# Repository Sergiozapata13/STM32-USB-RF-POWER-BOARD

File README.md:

# STM32-USB-RF-POWER-BOARD

## Overview
STM32-based embedded board integrating USB, RF transceiver, and regulated power supply.
Designed in KiCad with focus on signal integrity, power distribution, EMI mitigation, and
robust hardware design practices.

The project demonstrates a complete PCB design workflow, from system architecture
definition and schematic design to PCB layout and manufacturability review.

---

## System Architecture
The board integrates the following functional blocks:

- STM32 microcontroller
- USB interface for power and data communication
- nRF24L01+ 2.4 GHz RF transceiver
- Regulated 3.3 V power supply derived from USB
- SWD interface for programming and debugging

---

## Power Architecture

The board is powered exclusively from the USB 5 V rail. Input protection is provided
by a resettable fuse (100 mA) and a ferrite bead (100 Ω @ 100 MHz) to limit overcurrent
conditions and attenuate high-frequency noise coming from the USB source.

A low-dropout linear regulator (XC6206P332MR) is used to generate the 3.3 V supply
required by the STM32 microcontroller and the RF transceiver. This regulator was
selected due to its low noise characteristics and simplicity, which are well suited
for low-current embedded applications (up to 200 mA).

Bulk capacitors are placed at both the regulator input and output to ensure stability
and reduce supply ripple. Reverse polarity protection was intentionally omitted, as the
USB connector is the only intended power source for the board.

---

## USB Design

The USB interface is implemented using a Micro-USB connector and provides both power
and data connectivity. The VBUS line is used as the sole power source for the board.

Electrostatic discharge (ESD) protection is provided by a USBLC6-2SC6 device placed
between the USB connector and the microcontroller. This device protects the D+ and D−
lines against ESD events while preserving signal integrity.

USB differential data lines are routed as a matched pair and clearly labeled to support
controlled impedance routing during PCB layout. Protection components are placed close
to the connector to minimize trace length and reduce exposure to ESD events.

---

## RF Design

The RF subsystem is based on the nRF24L01+ 2.4 GHz transceiver, interfaced with the STM32
microcontroller through an SPI interface. The device is powered from the 3.3 V rail,
with dedicated local decoupling capacitors placed close to the VDD and VDD_PA pins to
ensure stable RF operation.

Special attention was given to power integrity for the RF section by providing adequate
bulk and high-frequency decoupling and following manufacturer reference design
guidelines.

### Antenna Matching Network

The RF output is routed through a discrete impedance matching network before reaching
an SMA connector. The matching network is implemented using lumped inductors and
capacitors, allowing flexibility for tuning during bring-up or testing.

The RF trace is intended to be routed as a 50 Ω controlled-impedance transmission line.
Component placement and routing were optimized to keep the RF path as short and direct
as possible, minimizing losses and parasitic effects.

### RF Crystal Oscillator

A dedicated 16 MHz crystal oscillator is used for the RF transceiver. Load capacitors
were selected based on the required load capacitance and estimated stray capacitance
of the PCB layout. A parallel resistor is included to aid oscillator startup and
improve stability.

Crystal components are placed close to the transceiver pins with short, symmetric
traces to minimize phase noise and sensitivity to external interference.

---

## PCB Layout Strategy

The PCB layout was developed with emphasis on signal integrity, power distribution,
and noise isolation between digital, RF, and power domains. Component placement was
driven by functional grouping, minimizing critical trace lengths and optimizing return
current paths.

High-frequency and noise-sensitive components, such as the RF transceiver and its
matching network, are placed close together to reduce parasitic effects. Power-related
components are grouped to form compact current loops, reducing EMI and voltage ripple.

USB differential pairs are routed together with consistent spacing and length matching,
and ground continuity is maintained under high-speed signals to ensure a clear return
path.

A compact board outline was selected to balance mechanical constraints, routing density,
and manufacturability.

---

## Hardware Validation and Design Status

The PCB was fully designed and reviewed at schematic and layout level; however, the
board was not manufactured or assembled.

Design validation focused on schematic correctness, component selection, and layout
best practices. Electrical rules checks (ERC) and design rule checks (DRC) were used to
verify connectivity, clearance, and manufacturability constraints.

The design is considered ready for fabrication. A bring-up and validation plan was
defined, including power rail verification, SWD programming, USB enumeration, and basic
RF communication tests.

Although physical validation was not performed, the project demonstrates a complete
end-to-end PCB design workflow, from system architecture definition to layout completion.

---

## Tools
- KiCad
- STM32CubeMX (pinout and reference configuration)

---

## Project Status
- Schematic and PCB layout completed
- Design reviewed with ERC/DRC verification
- Ready for fabrication

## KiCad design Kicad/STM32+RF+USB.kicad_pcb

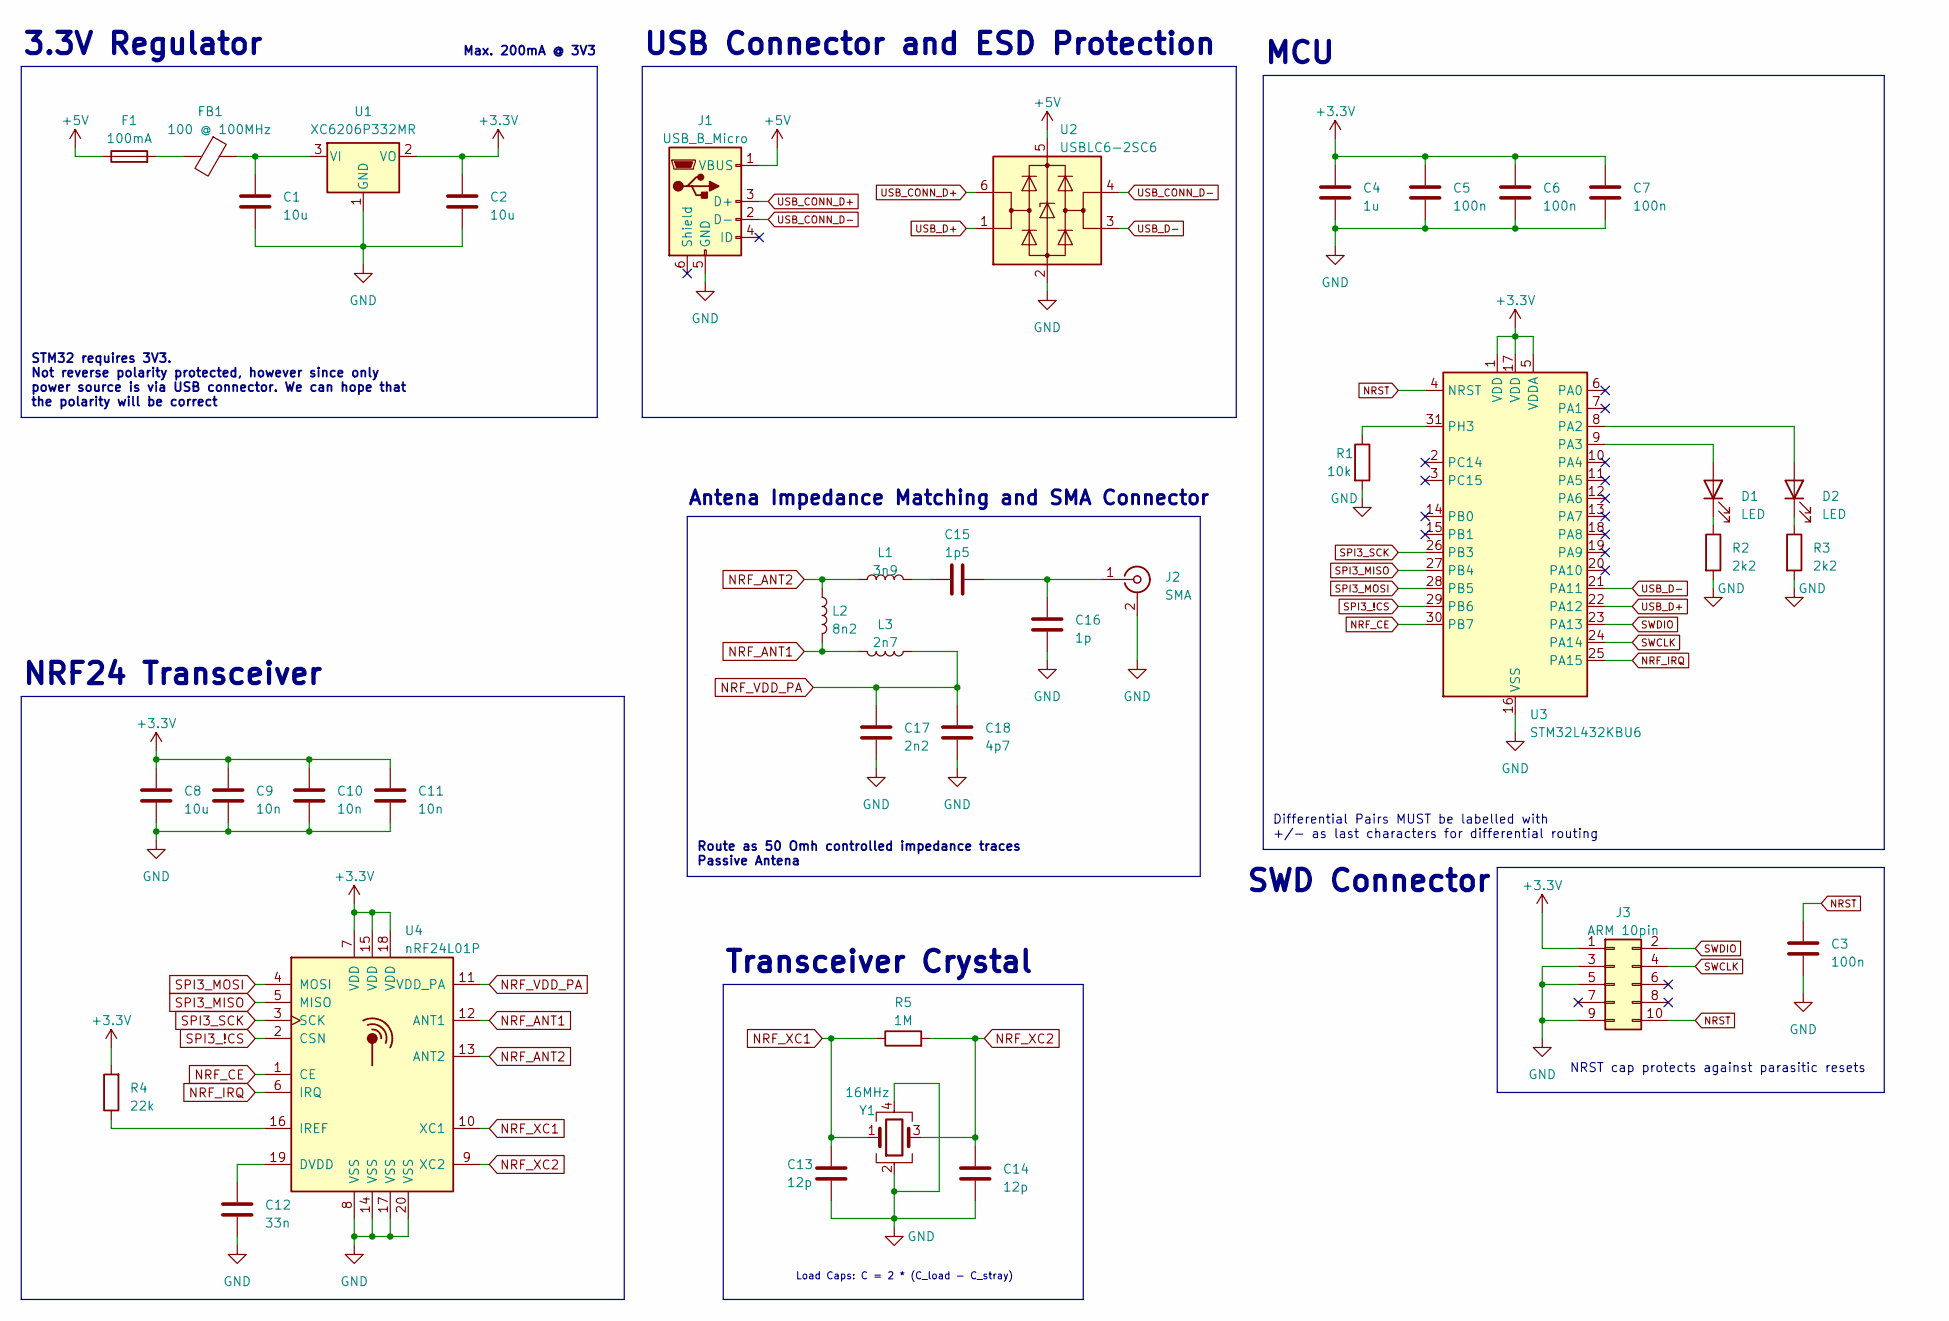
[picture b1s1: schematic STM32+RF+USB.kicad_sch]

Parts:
C1, C2, C8: 10u; C_0603_1608Metric
C3, C5, C6, C7: 100n; C_0402_1005Metric
C4: 1u; C_0402_1005Metric
C9, C10, C11: 10n; C_0402_1005Metric
C12: 33n; C_0402_1005Metric
C13, C14: 12p; C_0402_1005Metric
C15: 1p5; C_0402_1005Metric
C16: 1p; C_0402_1005Metric
C17: 2n2; C_0402_1005Metric
C18: 4p7; C_0402_1005Metric
D1, D2: LED; LED_0603_1608Metric
F1: 100mA; Fuse_1206_3216Metric
FB1: 100 @ 100MHz; L_0805_2012Metric
J1: USB_B_Micro; USB_Micro-B_Molex-105017-0001
J2: SMA; SMA_Samtec_SMA-J-P-X-ST-EM1_EdgeMount
J3: ARM 10pin; PinHeader_2x05_P1.27mm_Vertical
L1: 3n9; L_0402_1005Metric
L2: 8n2; L_0402_1005Metric
L3: 2n7; L_0402_1005Metric
R1: 10k; R_0402_1005Metric
R2, R3: 2k2; R_0603_1608Metric
R4: 22k; R_0402_1005Metric
R5: 1M; R_0402_1005Metric
U1: XC6206P332MR; SOT-23-3
U2: USBLC6-2SC6; SOT-23-6
U3: STM32L432KBU6; QFN-32-1EP_5x5mm_P0.5mm_EP3.45x3.45mm
U4: nRF24L01P; QFN-20-1EP_4x4mm_P0.5mm_EP2.5x2.5mm
Y1: 16MHz; Crystal_SMD_3225-4Pin_3.2x2.5mm

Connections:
+3.3V: C2.1, C4.1, C5.1, C6.1, C7.1, C8.1, C9.1, C10.1, C11.1, J3.1, R4.2, U1.2 (VO), U3.1 (VDD), U3.5 (VDDA), U3.17 (VDD), U4.7 (VDD), U4.15 (VDD), U4.18 (VDD)
+5V: F1.1, J1.1 (VBUS), U2.5 (VBUS)
GND: C1.2, C2.2, C3.2, C4.2, C5.2, C6.2, C7.2, C8.2, C9.2, C10.2, C11.2, C12.2, C13.2, C14.2, C16.1, C17.1, C18.1, J1.5 (GND), J2.2 (Ext), J3.3, J3.5, J3.9, R1.2, R2.2, R3.2, U1.1 (GND), U2.2 (GND), U3.16 (VSS), U3.32 (VSS), U3.33 (VSS), U4.8 (VSS), U4.14 (VSS), U4.17 (VSS), U4.20 (VSS), Y1.2, Y1.4
NRF_ANT1: L2.2, L3.2, U4.12 (ANT1)
NRF_ANT2: L1.1, L2.1, U4.13 (ANT2)
NRF_CE: U3.30 (PB7), U4.1 (CE)
NRF_IRQ: U3.25 (PA15), U4.6 (IRQ)
NRF_VDD_PA: C17.2, C18.2, L3.1, U4.11 (VDD_PA)
NRF_XC1: C13.1, R5.1, U4.10 (XC1), Y1.1
NRF_XC2: C14.1, R5.2, U4.9 (XC2), Y1.3
NRST: C3.1, J3.10, U3.4 (NRST)
unnamed: C15.1, L1.2
unnamed: D1.2 (A), U3.9 (PA3)
unnamed: D1.1 (K), R2.1
unnamed: D2.2 (A), U3.8 (PA2)
unnamed: D2.1 (K), R3.1
unnamed: F1.2, FB1.2
unnamed: C15.2, C16.2, J2.1 (In)
unnamed: C1.1, FB1.1, U1.3 (VI)
unnamed: R1.1, U3.31 (PH3)
unnamed: C12.1, U4.19 (DVDD)
unnamed: R4.1, U4.16 (IREF)
SPI3_!CS: U3.29 (PB6), U4.2 (CSN)
SPI3_MISO: U3.27 (PB4), U4.5 (MISO)
SPI3_MOSI: U3.28 (PB5), U4.4 (MOSI)
SPI3_SCK: U3.26 (PB3), U4.3 (SCK)
SWCLK: J3.4, U3.24 (PA14)
SWDIO: J3.2, U3.23 (PA13)
USB_CONN_D+: J1.3 (D+), U2.6 (I/O1)
USB_CONN_D-: J1.2 (D-), U2.4 (I/O2)
USB_D+: U2.1 (I/O1), U3.22 (PA12)
USB_D-: U2.3 (I/O2), U3.21 (PA11)

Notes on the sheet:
Load Caps: C = 2 * (C_load - C_stray)
Max. 200mA @ 3V3
SWD Connector
Differential Pairs MUST be labelled with +/- as last characters for differential routing
Transceiver Crystal
USB Connector and ESD Protection
STM32 requires 3V3. Not reverse polarity protected, however since only power source is via USB connector. We can hope that the polarity will be correct
Route as 50 Omh controlled impedance traces Passive Antena
MCU
Antena Impedance Matching and SMA Connector
NRST cap protects against parasitic resets
NRF24 Transceiver
3.3V Regulator

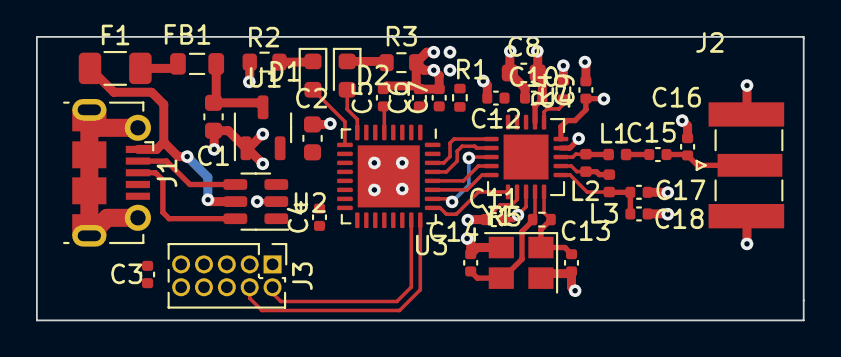
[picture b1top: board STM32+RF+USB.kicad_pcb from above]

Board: 4 copper layers, 42.6 x 15.8 mm, 38 parts (0 on the bottom side), 32 nets.

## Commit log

2026-01-22 Enhance README with detailed project information
    Expanded the README with sections on system architecture, power architecture, USB design, RF design, PCB layout strategy, hardware validation, tools, and project status.
2026-01-23 Document power architecture in README
    Added detailed explanation of the power architecture, including design considerations for voltage regulation and noise performance.
2026-01-23 Refine power architecture description in README
    Updated the power architecture section for clarity and detail.
2026-01-23 Revise README for improved clarity and completeness
    Updated README to enhance clarity and detail in project descriptions and design practices.
2026-01-23 Fix image link for NRF24 transceiver schematic
